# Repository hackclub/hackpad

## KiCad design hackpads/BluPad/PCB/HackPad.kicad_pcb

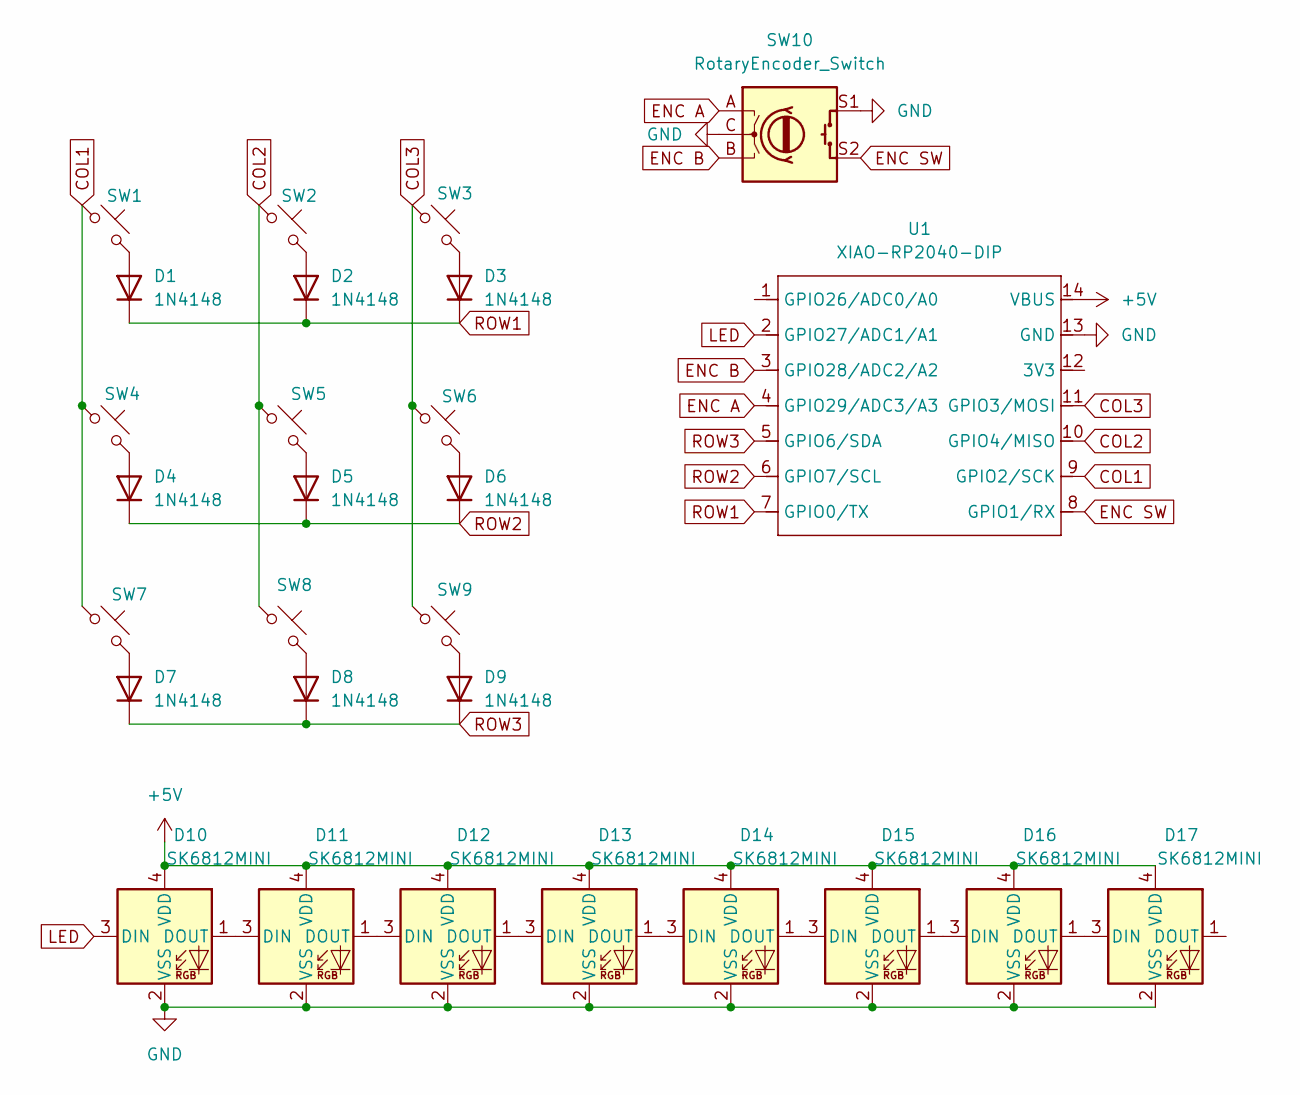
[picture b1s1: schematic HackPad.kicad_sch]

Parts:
D1, D2, D3, D4, D5, D6, D7, D8, D9: 1N4148; D_DO-35_SOD27_P7.62mm_Horizontal
D10, D11, D12, D13, D14, D15, D16, D17: SK6812MINI; LED_SK6812MINI_PLCC4_3.5x3.5mm_P1.75mm
SW1, SW2, SW3, SW4, SW5, SW6, SW7, SW8, SW9: SW_Push_45deg; SW_Cherry_MX_1.00u_PCB
SW10: RotaryEncoder_Switch; RotaryEncoder_Alps_EC11E-Switch_Vertical_H20mm
U1: XIAO-RP2040-DIP

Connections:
+5V: D10.4 (VDD), D11.4 (VDD), D12.4 (VDD), D13.4 (VDD), D14.4 (VDD), D15.4 (VDD), D16.4 (VDD), D17.4 (VDD), U1.14 (VBUS)
COL1: SW1.1, SW4.1, SW7.1, U1.9 (GPIO2/SCK)
COL2: SW2.1, SW5.1, SW8.1, U1.10 (GPIO4/MISO)
COL3: SW3.1, SW6.1, SW9.1, U1.11 (GPIO3/MOSI)
ENC A: SW10.A, U1.4 (GPIO29/ADC3/A3)
ENC B: SW10.B, U1.3 (GPIO28/ADC2/A2)
ENC SW: SW10.S2, U1.8 (GPIO1/RX)
GND: D10.2 (VSS), D11.2 (VSS), D12.2 (VSS), D13.2 (VSS), D14.2 (VSS), D15.2 (VSS), D16.2 (VSS), D17.2 (VSS), SW10.C, SW10.S1, U1.13 (GND)
LED: D10.3 (DIN), U1.2 (GPIO27/ADC1/A1)
unnamed: D1.2 (A), SW1.2
unnamed: D2.2 (A), SW2.2
unnamed: D3.2 (A), SW3.2
unnamed: D4.2 (A), SW4.2
unnamed: D5.2 (A), SW5.2
unnamed: D6.2 (A), SW6.2
unnamed: D7.2 (A), SW7.2
unnamed: D8.2 (A), SW8.2
unnamed: D9.2 (A), SW9.2
unnamed: D10.1 (DOUT), D11.3 (DIN)
unnamed: D11.1 (DOUT), D12.3 (DIN)
unnamed: D12.1 (DOUT), D13.3 (DIN)
unnamed: D13.1 (DOUT), D14.3 (DIN)
unnamed: D14.1 (DOUT), D15.3 (DIN)
unnamed: D15.1 (DOUT), D16.3 (DIN)
unnamed: D16.1 (DOUT), D17.3 (DIN)
ROW1: D1.1 (K), D2.1 (K), D3.1 (K), U1.7 (GPIO0/TX)
ROW2: D4.1 (K), D5.1 (K), D6.1 (K), U1.6 (GPIO7/SCL)
ROW3: D7.1 (K), D8.1 (K), D9.1 (K), U1.5 (GPIO6/SDA)

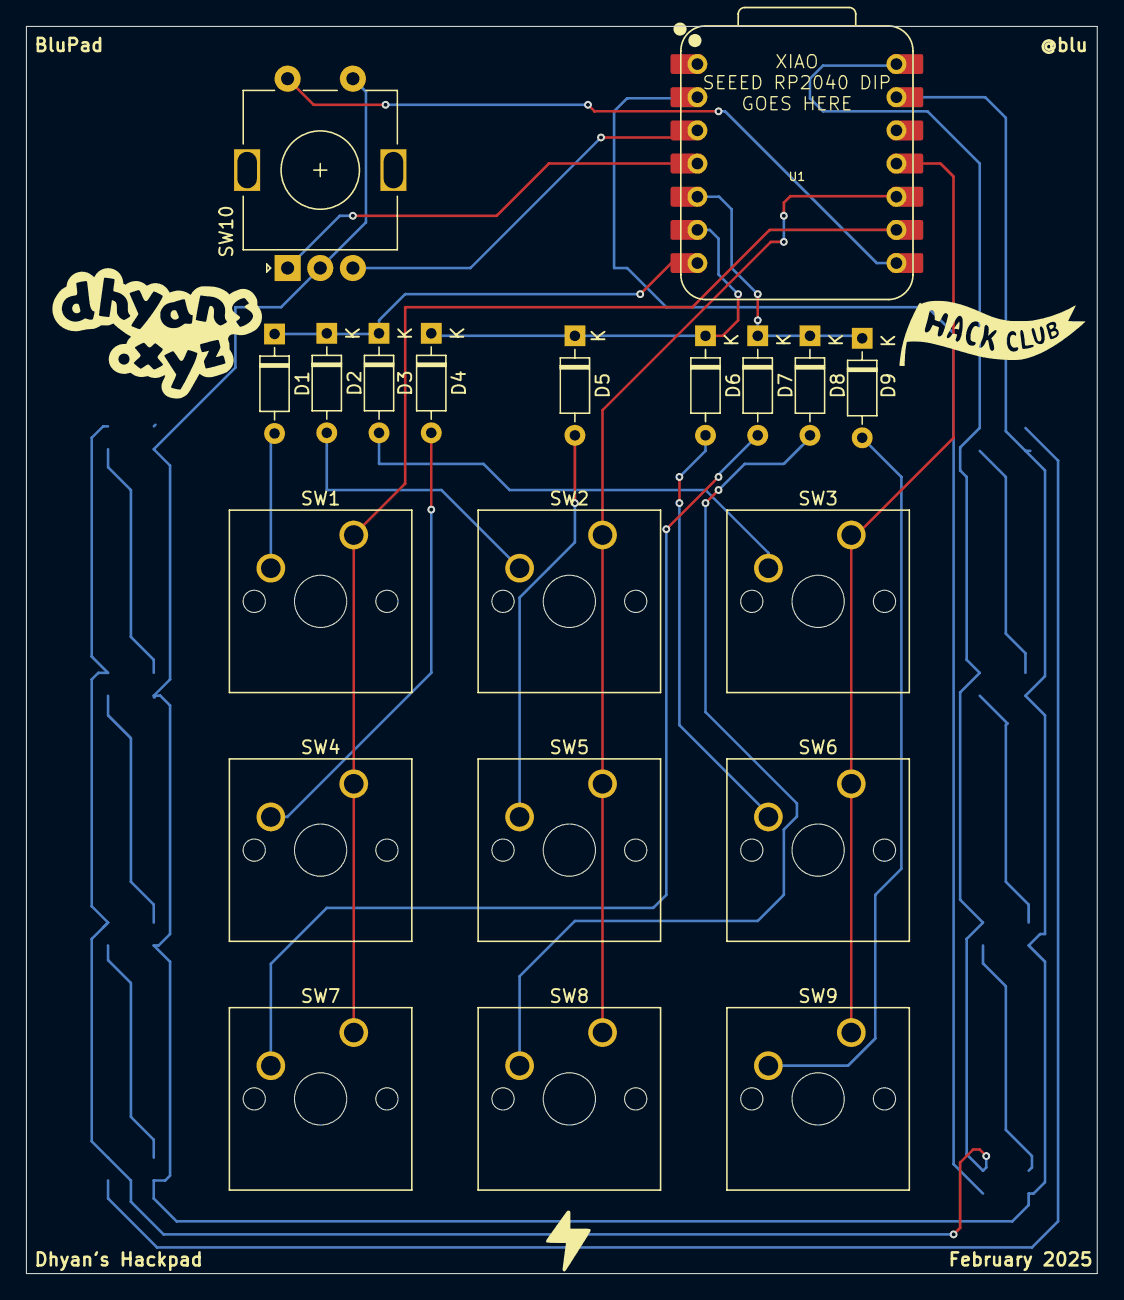
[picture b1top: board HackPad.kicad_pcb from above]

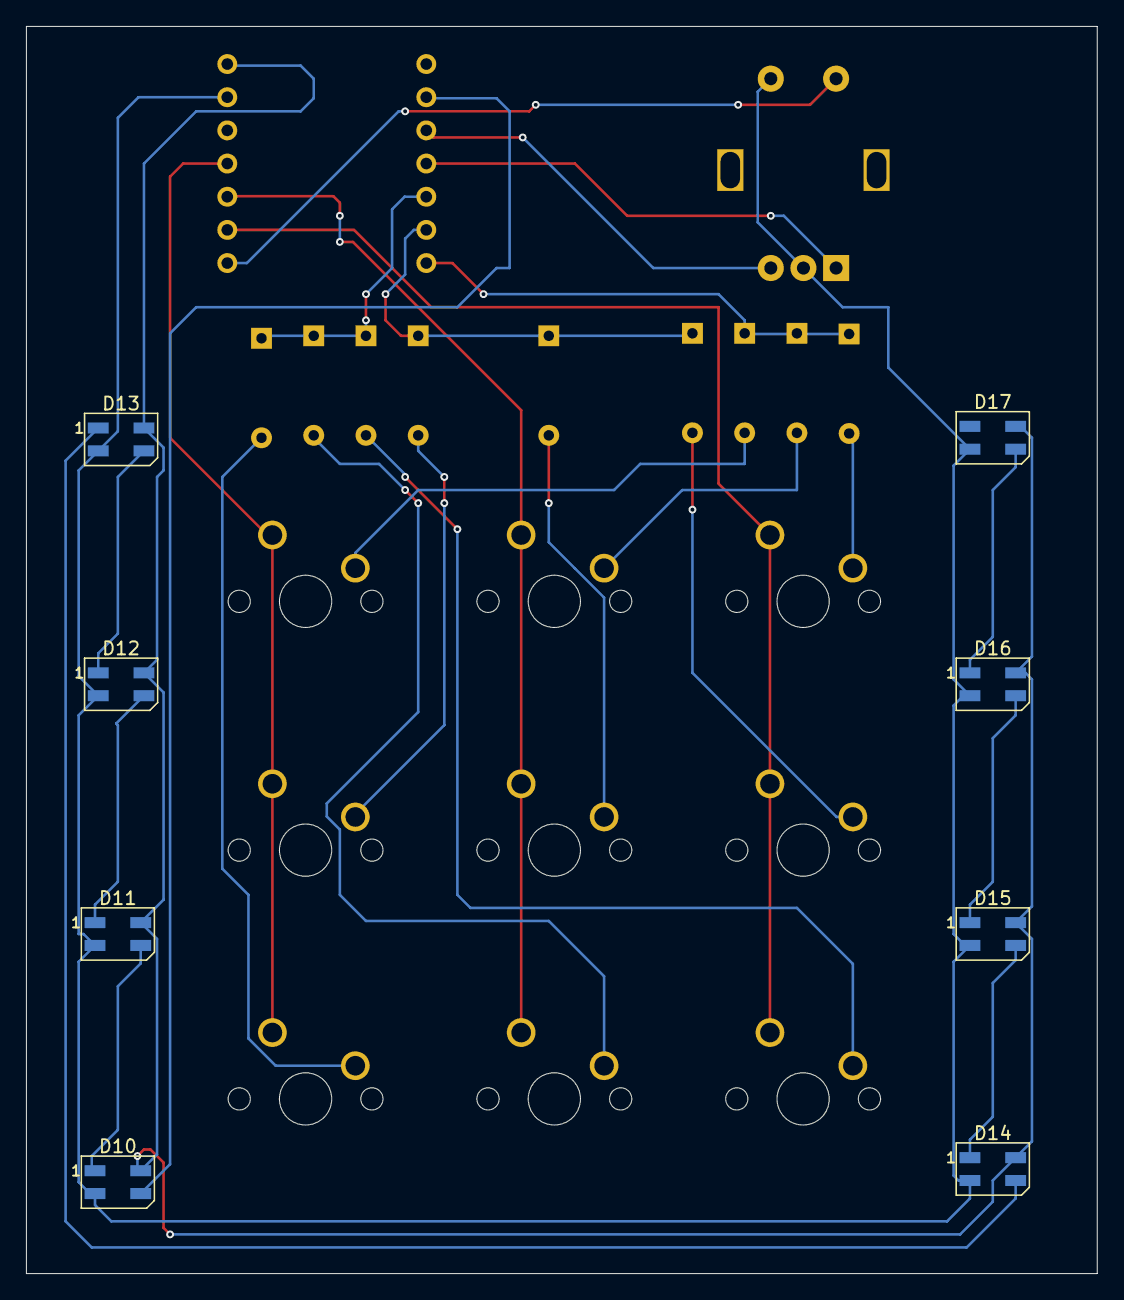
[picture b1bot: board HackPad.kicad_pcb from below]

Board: 2 copper layers, 82.0 x 95.5 mm, 28 parts (8 on the bottom side), 28 nets.

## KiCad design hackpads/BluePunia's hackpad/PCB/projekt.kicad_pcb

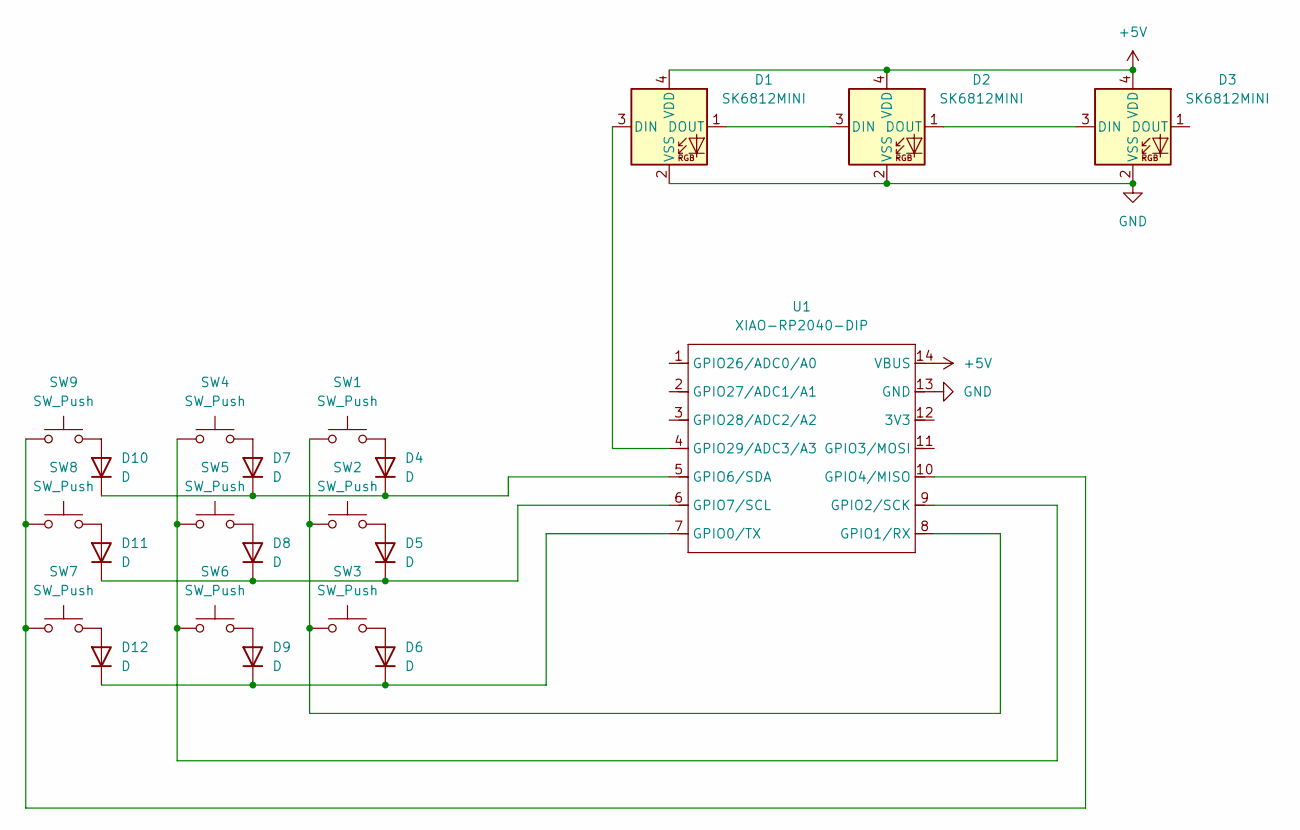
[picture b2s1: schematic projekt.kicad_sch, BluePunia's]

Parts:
D1, D2, D3: SK6812MINI; LED_SK6812MINI_PLCC4_3.5x3.5mm_P1.75mm
D4, D5, D6, D7, D8, D9, D10, D11, D12: D; D_DO-41_SOD81_P7.62mm_Horizontal
SW1, SW2, SW3, SW4, SW5, SW6, SW7, SW8, SW9: SW_Push; SW_Cherry_MX_1.00u_PCB
U1: XIAO-RP2040-DIP

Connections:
+5V: D1.4 (VDD), D2.4 (VDD), D3.4 (VDD), U1.14 (VBUS)
GND: D1.2 (VSS), D2.2 (VSS), D3.2 (VSS), U1.13 (GND)
unnamed: D1.3 (DIN), U1.4 (GPIO29/ADC3/A3)
unnamed: D1.1 (DOUT), D2.3 (DIN)
unnamed: D2.1 (DOUT), D3.3 (DIN)
unnamed: D4.2 (A), SW1.2
unnamed: D5.2 (A), SW2.2
unnamed: D6.2 (A), SW3.2
unnamed: D7.2 (A), SW4.2
unnamed: D8.2 (A), SW5.2
unnamed: D9.2 (A), SW6.2
unnamed: D10.2 (A), SW9.2
unnamed: D4.1 (K), D7.1 (K), D10.1 (K), U1.5 (GPIO6/SDA)
unnamed: D11.2 (A), SW8.2
unnamed: D5.1 (K), D8.1 (K), D11.1 (K), U1.6 (GPIO7/SCL)
unnamed: D12.2 (A), SW7.2
unnamed: D6.1 (K), D9.1 (K), D12.1 (K), U1.7 (GPIO0/TX)
unnamed: SW1.1, SW2.1, SW3.1, U1.8 (GPIO1/RX)
unnamed: SW4.1, SW5.1, SW6.1, U1.9 (GPIO2/SCK)
unnamed: SW7.1, SW8.1, SW9.1, U1.10 (GPIO4/MISO)

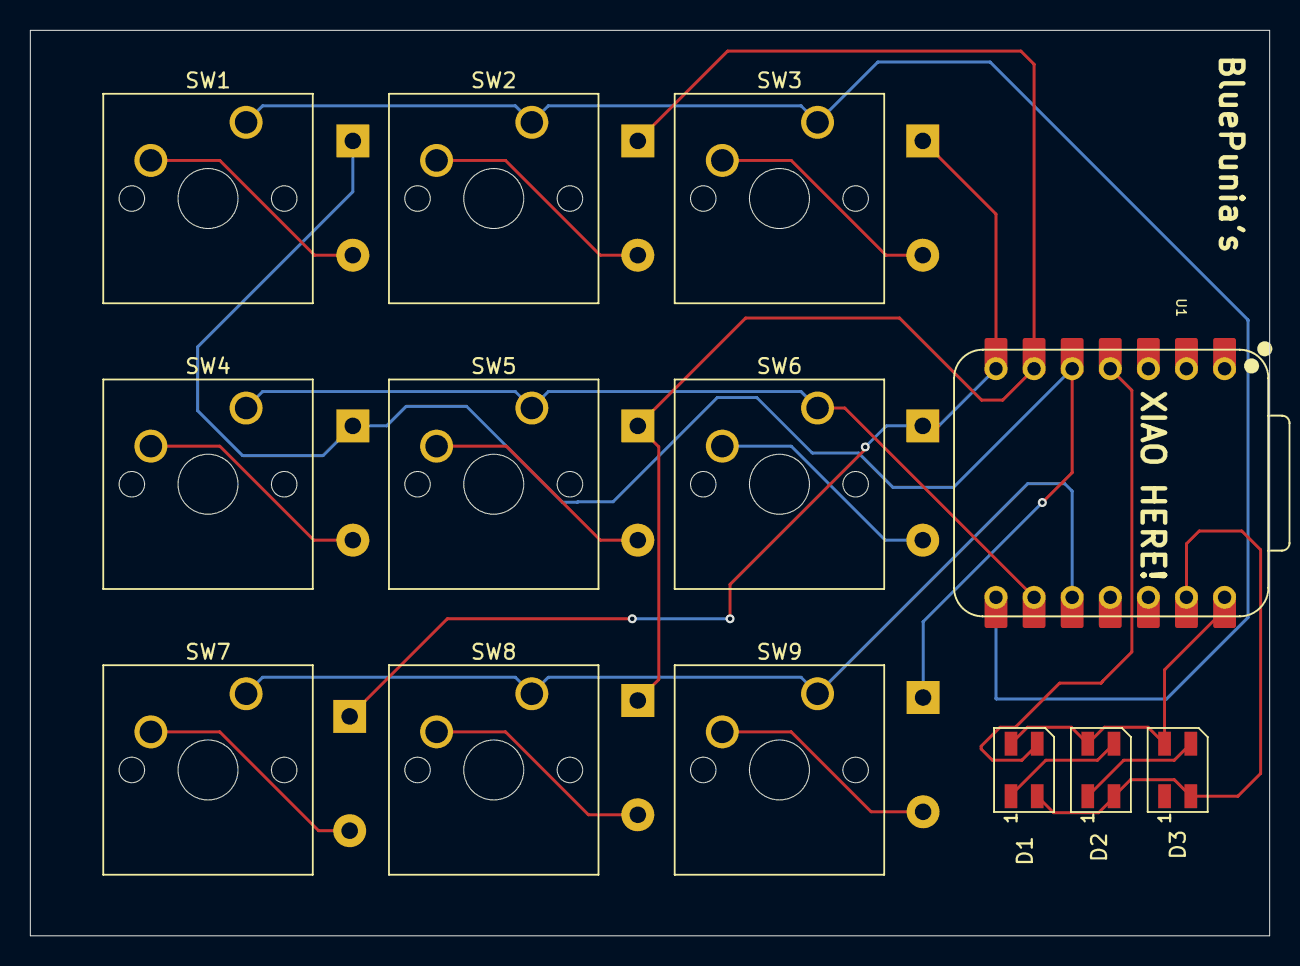
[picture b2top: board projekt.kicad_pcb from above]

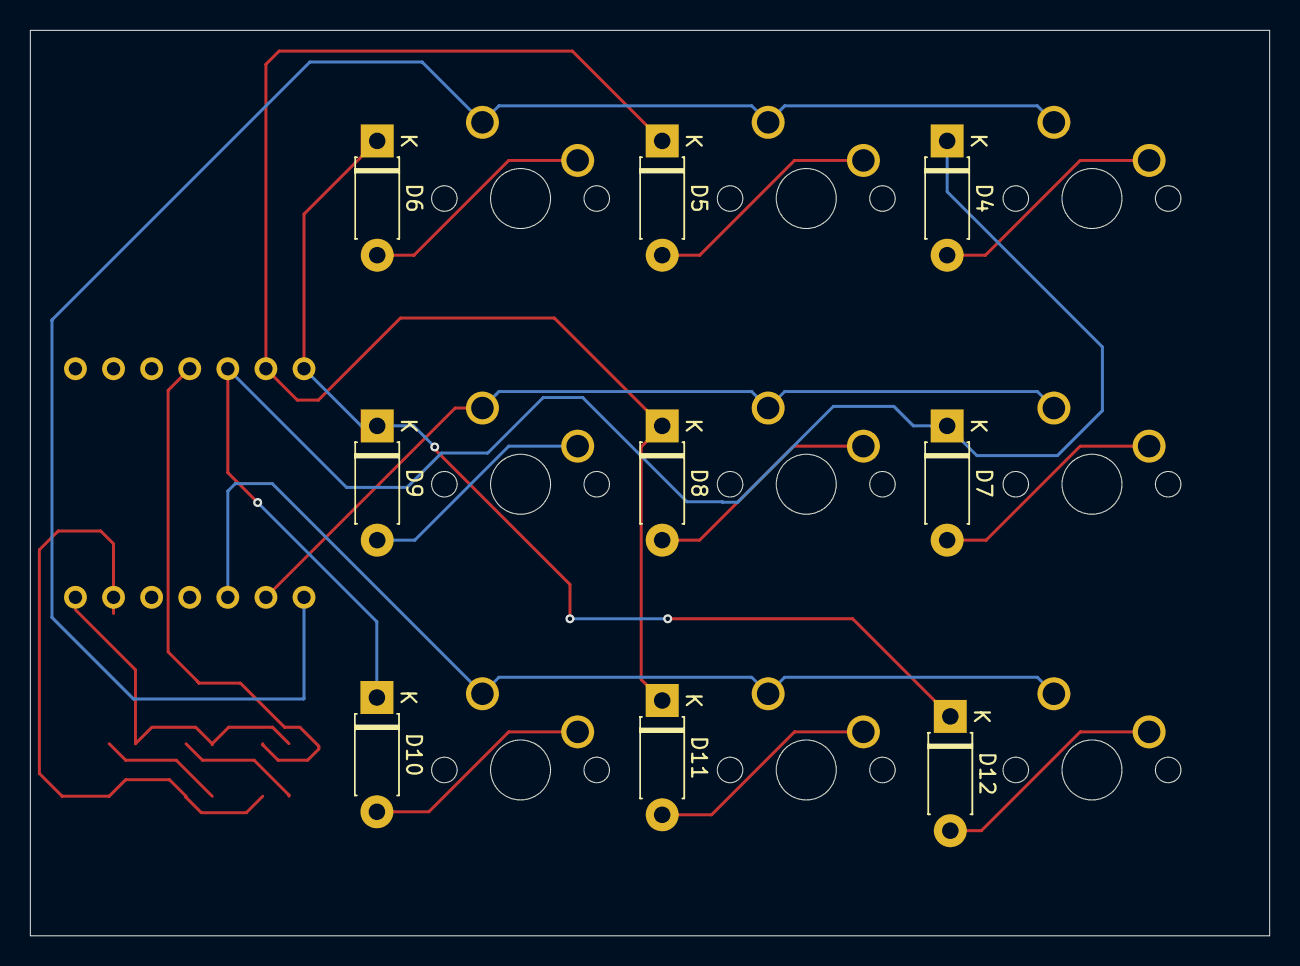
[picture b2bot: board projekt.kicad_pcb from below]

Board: 2 copper layers, 82.6 x 60.4 mm, 22 parts (9 on the bottom side), 20 nets.

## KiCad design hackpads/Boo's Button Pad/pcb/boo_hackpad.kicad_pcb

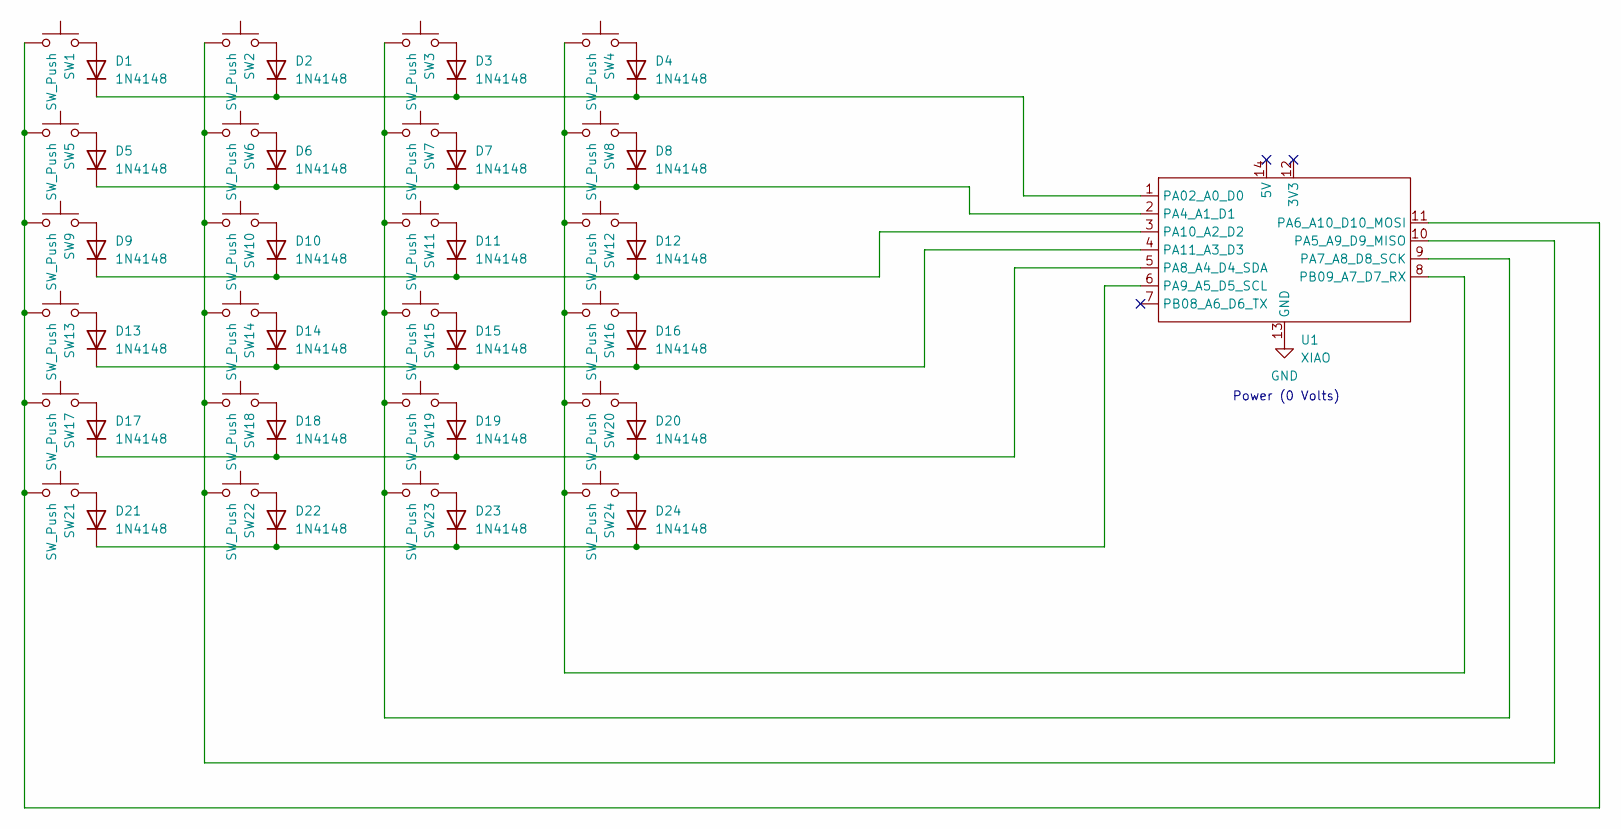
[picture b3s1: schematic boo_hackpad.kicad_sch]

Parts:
D1, D2, D3, D4, D5, D6, D7, D8, D9, D10, D11, D12, D13, D14, D15, D16, D17, D18, D19, D20, D21, D22, D23, D24: 1N4148; D_DO-35_SOD27_P7.62mm_Horizontal
SW1, SW2, SW3, SW4, SW5, SW6, SW7, SW8, SW9, SW10, SW11, SW12, SW13, SW14, SW15, SW16, SW17, SW18, SW19, SW20, SW21, SW22, SW23, SW24: SW_Push; SW_Cherry_MX_1.00u_PCB
U1: XIAO; XIAO-Generic-Hybrid-14P-2.54-21X17.8MM

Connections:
GND: U1.13 (GND)
unnamed: D1.2 (A), SW1.2
unnamed: D1.1 (K), D2.1 (K), D3.1 (K), D4.1 (K), U1.1 (PA02_A0_D0)
unnamed: D2.2 (A), SW2.2
unnamed: D3.2 (A), SW3.2
unnamed: D4.2 (A), SW4.2
unnamed: D5.2 (A), SW5.2
unnamed: D5.1 (K), D6.1 (K), D7.1 (K), D8.1 (K), U1.2 (PA4_A1_D1)
unnamed: D6.2 (A), SW6.2
unnamed: D7.2 (A), SW7.2
unnamed: D8.2 (A), SW8.2
unnamed: D9.2 (A), SW9.2
unnamed: D10.2 (A), SW10.2
unnamed: D9.1 (K), D10.1 (K), D11.1 (K), D12.1 (K), U1.3 (PA10_A2_D2)
unnamed: D11.2 (A), SW11.2
unnamed: D12.2 (A), SW12.2
unnamed: D13.2 (A), SW13.2
unnamed: D13.1 (K), D14.1 (K), D15.1 (K), D16.1 (K), U1.4 (PA11_A3_D3)
unnamed: D14.2 (A), SW14.2
unnamed: D15.2 (A), SW15.2
unnamed: D16.2 (A), SW16.2
unnamed: D17.2 (A), SW17.2
unnamed: D17.1 (K), D18.1 (K), D19.1 (K), D20.1 (K), U1.5 (PA8_A4_D4_SDA)
unnamed: D18.2 (A), SW18.2
unnamed: D19.2 (A), SW19.2
unnamed: D20.2 (A), SW20.2
unnamed: D21.2 (A), SW21.2
unnamed: D21.1 (K), D22.1 (K), D23.1 (K), D24.1 (K), U1.6 (PA9_A5_D5_SCL)
unnamed: D22.2 (A), SW22.2
unnamed: D23.2 (A), SW23.2
unnamed: D24.2 (A), SW24.2
unnamed: SW2.1, SW6.1, SW10.1, SW14.1, SW18.1, SW22.1, U1.10 (PA5_A9_D9_MISO)
unnamed: SW1.1, SW5.1, SW9.1, SW13.1, SW17.1, SW21.1, U1.11 (PA6_A10_D10_MOSI)
unnamed: SW3.1, SW7.1, SW11.1, SW15.1, SW19.1, SW23.1, U1.9 (PA7_A8_D8_SCK)
unnamed: SW4.1, SW8.1, SW12.1, SW16.1, SW20.1, SW24.1, U1.8 (PB09_A7_D7_RX)

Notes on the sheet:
Power (0 Volts)

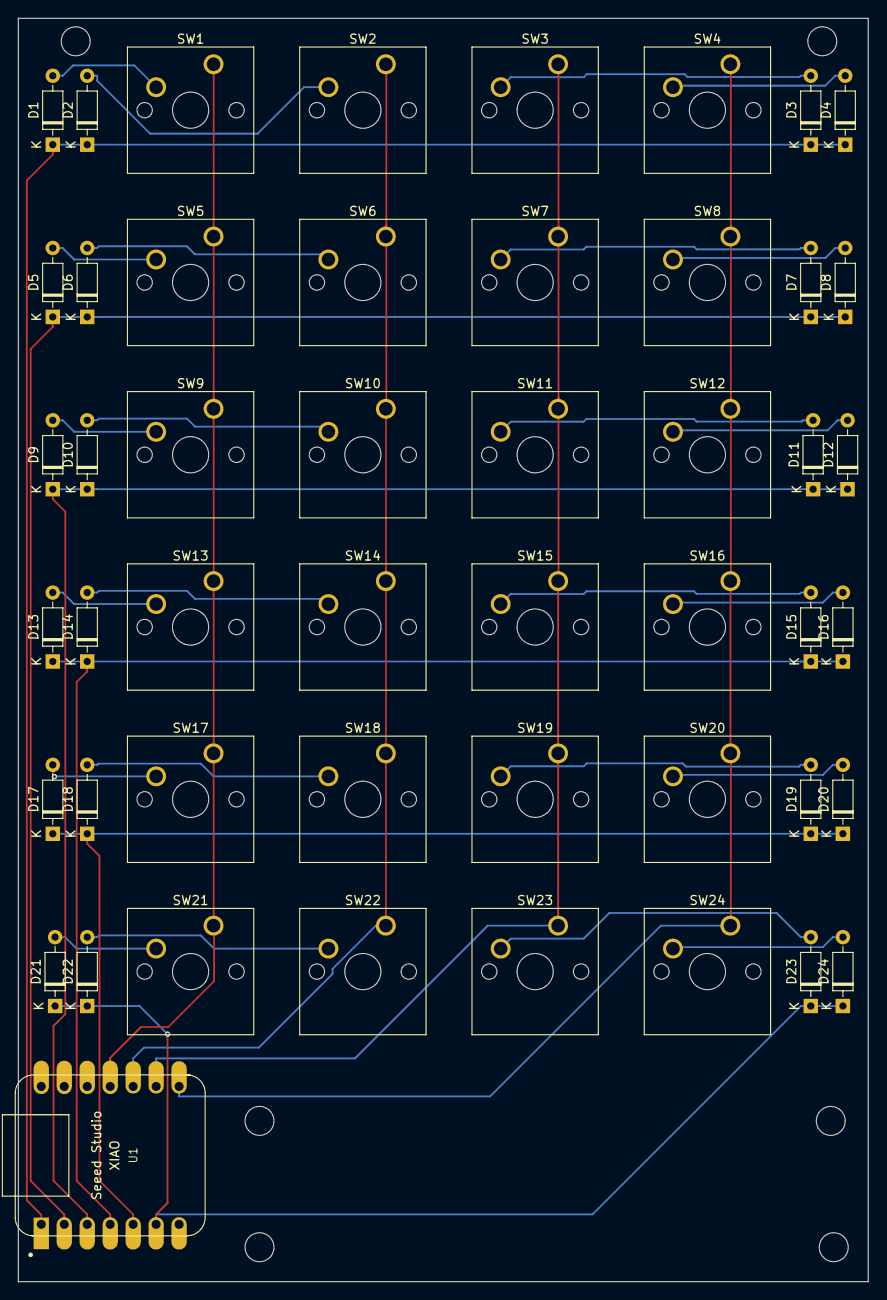
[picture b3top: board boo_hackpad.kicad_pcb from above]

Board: 2 copper layers, 94.0 x 139.7 mm, 49 parts (0 on the bottom side), 34 nets.

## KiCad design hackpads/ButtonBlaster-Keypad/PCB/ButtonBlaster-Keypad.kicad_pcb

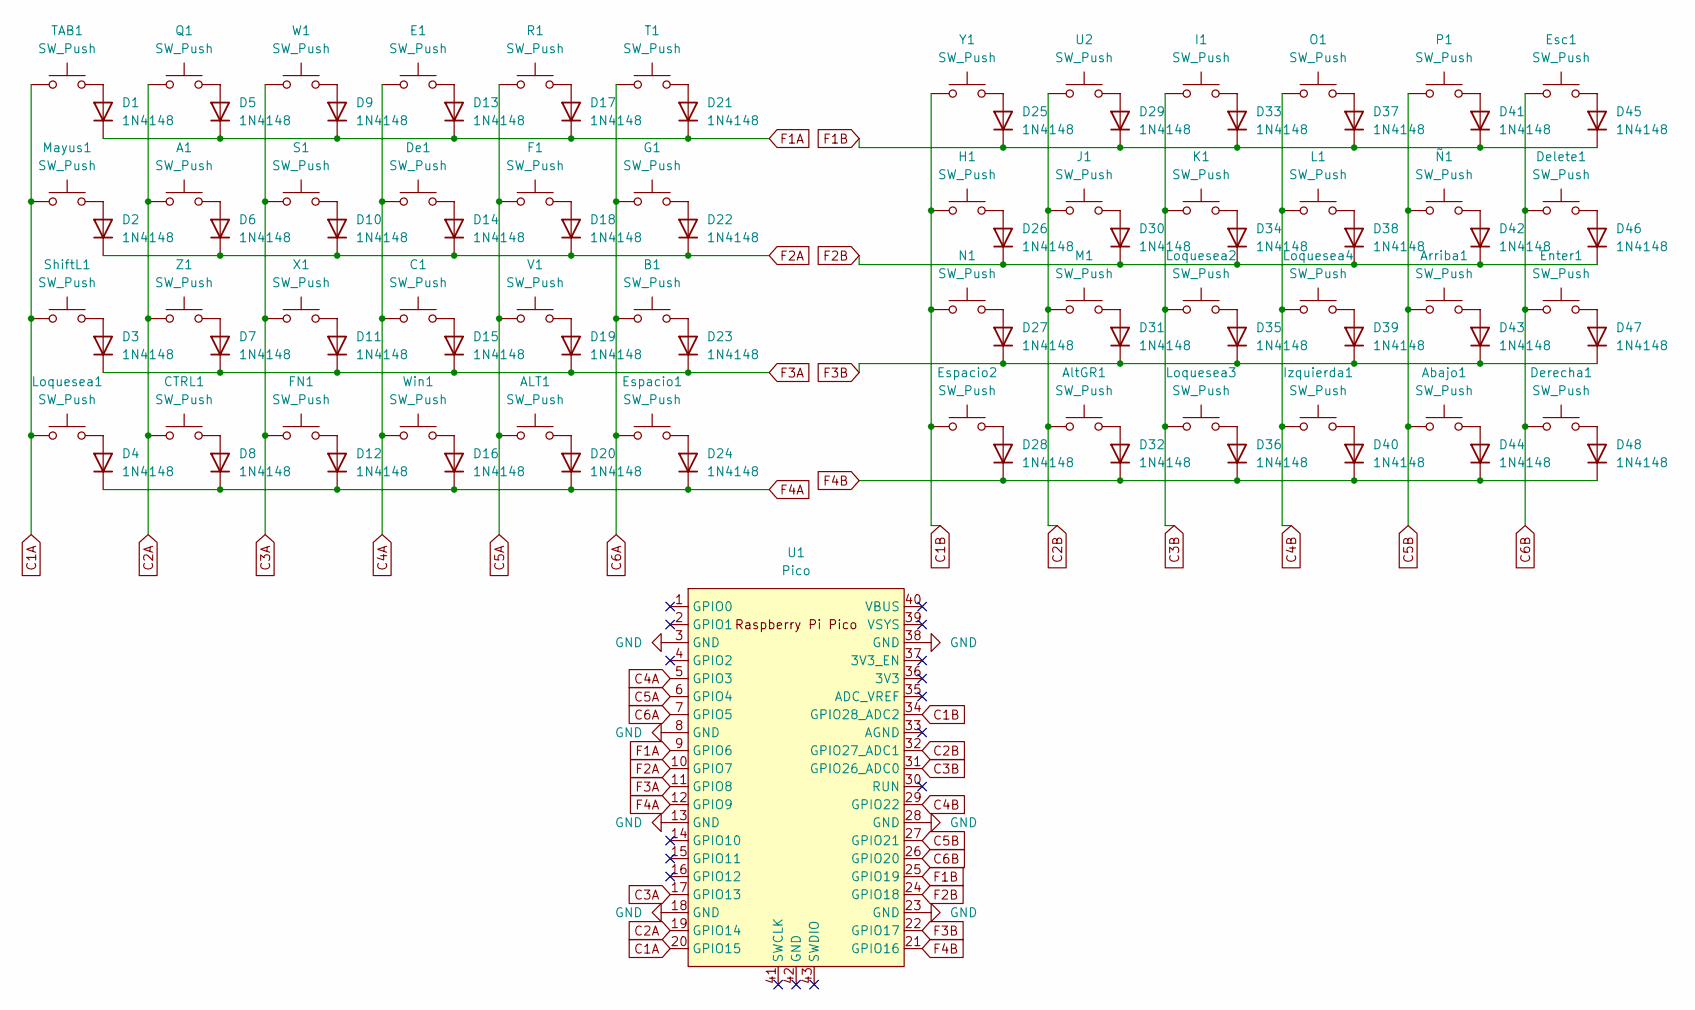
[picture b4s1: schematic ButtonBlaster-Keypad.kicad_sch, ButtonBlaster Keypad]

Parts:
A1: SW_Push; SW_Cherry_MX_1.00u_PCB
ALT1: SW_Push; SW_Cherry_MX_1.00u_PCB
Abajo1: SW_Push; SW_Cherry_MX_1.00u_PCB
AltGR1: SW_Push; SW_Cherry_MX_1.00u_PCB
Arriba1: SW_Push; SW_Cherry_MX_1.00u_PCB
B1: SW_Push; SW_Cherry_MX_1.00u_PCB
C1: SW_Push; SW_Cherry_MX_1.00u_PCB
CTRL1: SW_Push; SW_Cherry_MX_1.00u_PCB
D1, D2, D3, D4, D5, D6, D7, D8, D9, D10, D11, D12, D13, D14, D15, D16, D17, D18, D19, D20, D21, D22, D23, D24, D25, D26, D27, D28, D29, D30, D31, D32, D33, D34, D35, D36, D37, D38, D39, D40, D41, D42, D43, D44, D45, D46, D47, D48: 1N4148; D_DO-35_SOD27_P7.62mm_Horizontal
De1: SW_Push; SW_Cherry_MX_1.00u_PCB
Delete1: SW_Push; SW_Cherry_MX_1.00u_PCB
Derecha1: SW_Push; SW_Cherry_MX_1.00u_PCB
E1: SW_Push; SW_Cherry_MX_1.00u_PCB
Enter1: SW_Push; SW_Cherry_MX_1.00u_PCB
Esc1: SW_Push; SW_Cherry_MX_1.00u_PCB
Espacio1, Espacio2: SW_Push; SW_Cherry_MX_1.00u_PCB
F1: SW_Push; SW_Cherry_MX_1.00u_PCB
FN1: SW_Push; SW_Cherry_MX_1.00u_PCB
G1: SW_Push; SW_Cherry_MX_1.00u_PCB
H1: SW_Push; SW_Cherry_MX_1.00u_PCB
I1: SW_Push; SW_Cherry_MX_1.00u_PCB
Izquierda1: SW_Push; SW_Cherry_MX_1.00u_PCB
J1: SW_Push; SW_Cherry_MX_1.00u_PCB
K1: SW_Push; SW_Cherry_MX_1.00u_PCB
L1: SW_Push; SW_Cherry_MX_1.00u_PCB
Loquesea1, Loquesea2, Loquesea3, Loquesea4: SW_Push; SW_Cherry_MX_1.00u_PCB
M1: SW_Push; SW_Cherry_MX_1.00u_PCB
Mayus1: SW_Push; SW_Cherry_MX_1.00u_PCB
N1: SW_Push; SW_Cherry_MX_1.00u_PCB
O1: SW_Push; SW_Cherry_MX_1.00u_PCB
P1: SW_Push; SW_Cherry_MX_1.00u_PCB
Q1: SW_Push; SW_Cherry_MX_1.00u_PCB
R1: SW_Push; SW_Cherry_MX_1.00u_PCB
S1: SW_Push; SW_Cherry_MX_1.00u_PCB
ShiftL1: SW_Push; SW_Cherry_MX_1.00u_PCB
T1: SW_Push; SW_Cherry_MX_1.00u_PCB
TAB1: SW_Push; SW_Cherry_MX_1.00u_PCB
U1: Pico; RPi_Pico_SMD_TH
U2: SW_Push; SW_Cherry_MX_1.00u_PCB
V1: SW_Push; SW_Cherry_MX_1.00u_PCB
W1: SW_Push; SW_Cherry_MX_1.00u_PCB
Win1: SW_Push; SW_Cherry_MX_1.00u_PCB
X1: SW_Push; SW_Cherry_MX_1.00u_PCB
Y1: SW_Push; SW_Cherry_MX_1.00u_PCB
Z1: SW_Push; SW_Cherry_MX_1.00u_PCB
Ñ1: SW_Push; SW_Cherry_MX_1.00u_PCB

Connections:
C1A: Loquesea1.1, Mayus1.1, ShiftL1.1, TAB1.1, U1.20 (GPIO15)
C1B: Espacio2.1, H1.1, N1.1, U1.34 (GPIO28_ADC2), Y1.1
C2A: A1.1, CTRL1.1, Q1.1, U1.19 (GPIO14), Z1.1
C2B: AltGR1.1, J1.1, M1.1, U1.32 (GPIO27_ADC1), U2.1
C3A: FN1.1, S1.1, U1.17 (GPIO13), W1.1, X1.1
C3B: I1.1, K1.1, Loquesea2.1, Loquesea3.1, U1.31 (GPIO26_ADC0)
C4A: C1.1, De1.1, E1.1, U1.5 (GPIO3), Win1.1
C4B: Izquierda1.1, L1.1, Loquesea4.1, O1.1, U1.29 (GPIO22)
C5A: ALT1.1, F1.1, R1.1, U1.6 (GPIO4), V1.1
C5B: Abajo1.1, Arriba1.1, P1.1, U1.27 (GPIO21), Ñ1.1
C6A: B1.1, Espacio1.1, G1.1, T1.1, U1.7 (GPIO5)
C6B: Delete1.1, Derecha1.1, Enter1.1, Esc1.1, U1.26 (GPIO20)
F1A: D1.1 (K), D5.1 (K), D9.1 (K), D13.1 (K), D17.1 (K), D21.1 (K), U1.9 (GPIO6)
F1B: D25.1 (K), D29.1 (K), D33.1 (K), D37.1 (K), D41.1 (K), D45.1 (K), U1.25 (GPIO19)
F2A: D2.1 (K), D6.1 (K), D10.1 (K), D14.1 (K), D18.1 (K), D22.1 (K), U1.10 (GPIO7)
F2B: D26.1 (K), D30.1 (K), D34.1 (K), D38.1 (K), D42.1 (K), D46.1 (K), U1.24 (GPIO18)
F3A: D3.1 (K), D7.1 (K), D11.1 (K), D15.1 (K), D19.1 (K), D23.1 (K), U1.11 (GPIO8)
F3B: D27.1 (K), D31.1 (K), D35.1 (K), D39.1 (K), D43.1 (K), D47.1 (K), U1.22 (GPIO17)
F4A: D4.1 (K), D8.1 (K), D12.1 (K), D16.1 (K), D20.1 (K), D24.1 (K), U1.12 (GPIO9)
F4B: D28.1 (K), D32.1 (K), D36.1 (K), D40.1 (K), D44.1 (K), D48.1 (K), U1.21 (GPIO16)
GND: U1.3 (GND), U1.8 (GND), U1.13 (GND), U1.18 (GND), U1.23 (GND), U1.28 (GND), U1.38 (GND)
unnamed: D1.2 (A), TAB1.2
unnamed: D2.2 (A), Mayus1.2
unnamed: D3.2 (A), ShiftL1.2
unnamed: D4.2 (A), Loquesea1.2
unnamed: D5.2 (A), Q1.2
unnamed: A1.2, D6.2 (A)
unnamed: D7.2 (A), Z1.2
unnamed: CTRL1.2, D8.2 (A)
unnamed: D9.2 (A), W1.2
unnamed: D10.2 (A), S1.2
unnamed: D11.2 (A), X1.2
unnamed: D12.2 (A), FN1.2
unnamed: D13.2 (A), E1.2
unnamed: D14.2 (A), De1.2
unnamed: C1.2, D15.2 (A)
unnamed: D16.2 (A), Win1.2
unnamed: D17.2 (A), R1.2
unnamed: D18.2 (A), F1.2
unnamed: D19.2 (A), V1.2
unnamed: ALT1.2, D20.2 (A)
unnamed: D21.2 (A), T1.2
unnamed: D22.2 (A), G1.2
unnamed: B1.2, D23.2 (A)
unnamed: D24.2 (A), Espacio1.2
unnamed: D25.2 (A), Y1.2
unnamed: D26.2 (A), H1.2
unnamed: D27.2 (A), N1.2
unnamed: D28.2 (A), Espacio2.2
unnamed: D29.2 (A), U2.2
unnamed: D30.2 (A), J1.2
unnamed: D31.2 (A), M1.2
unnamed: AltGR1.2, D32.2 (A)
unnamed: D33.2 (A), I1.2
unnamed: D34.2 (A), K1.2
unnamed: D35.2 (A), Loquesea2.2
unnamed: D36.2 (A), Loquesea3.2
unnamed: D37.2 (A), O1.2
unnamed: D38.2 (A), L1.2
unnamed: D39.2 (A), Loquesea4.2
unnamed: D40.2 (A), Izquierda1.2
unnamed: D41.2 (A), P1.2
unnamed: D42.2 (A), Ñ1.2
unnamed: Arriba1.2, D43.2 (A)
unnamed: Abajo1.2, D44.2 (A)
unnamed: D45.2 (A), Esc1.2
unnamed: D46.2 (A), Delete1.2
unnamed: D47.2 (A), Enter1.2
unnamed: D48.2 (A), Derecha1.2

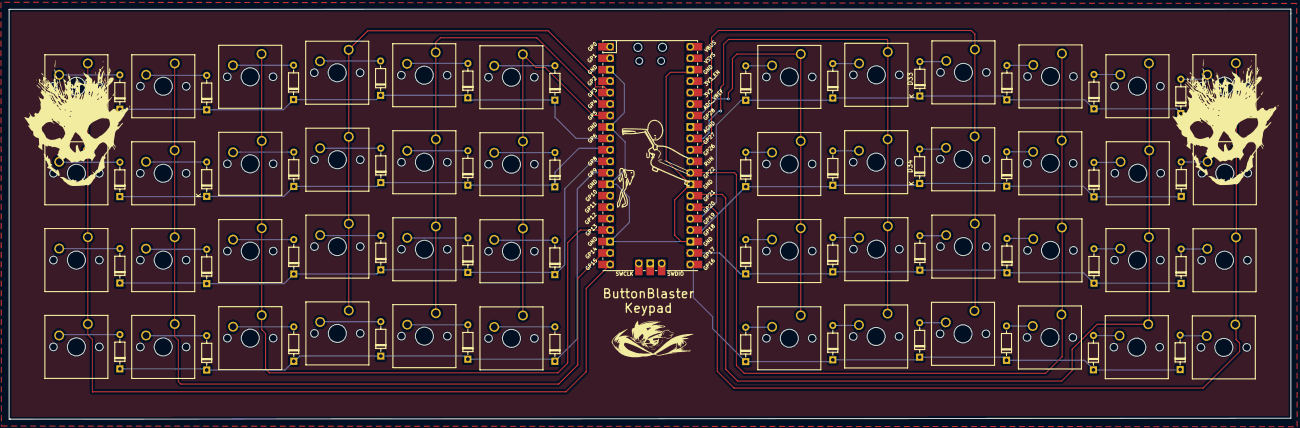
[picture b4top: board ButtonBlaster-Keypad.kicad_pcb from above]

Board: 2 copper layers, 284.1 x 90.9 mm, 97 parts (0 on the bottom side), 69 nets.

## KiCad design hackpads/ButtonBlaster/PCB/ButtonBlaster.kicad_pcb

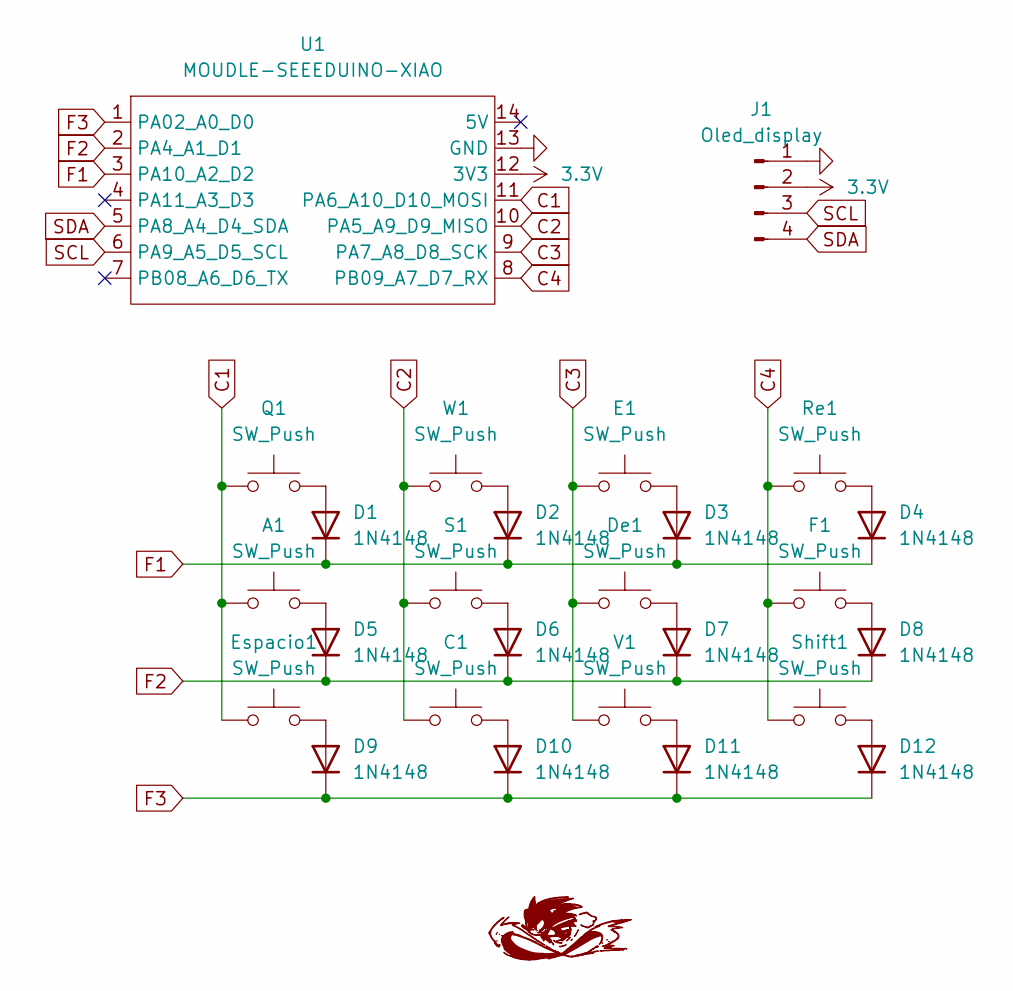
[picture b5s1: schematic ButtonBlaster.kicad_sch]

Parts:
A1: SW_Push; SW_Cherry_MX_1.00u_PCB
C1: SW_Push; SW_Cherry_MX_1.00u_PCB
D1, D2, D3, D4, D5, D6, D7, D8, D9, D10, D11, D12: 1N4148; D_DO-35_SOD27_P7.62mm_Horizontal
De1: SW_Push; SW_Cherry_MX_1.00u_PCB
E1: SW_Push; SW_Cherry_MX_1.00u_PCB
Espacio1: SW_Push; SW_Cherry_MX_1.00u_PCB
F1: SW_Push; SW_Cherry_MX_1.00u_PCB
J1: Oled_display; SSD1306-0.91-OLED-4pin-128x32
Q1: SW_Push; SW_Cherry_MX_1.00u_PCB
Re1: SW_Push; SW_Cherry_MX_1.00u_PCB
S1: SW_Push; SW_Cherry_MX_1.00u_PCB
Shift1: SW_Push; SW_Cherry_MX_1.00u_PCB
U1: MOUDLE-SEEEDUINO-XIAO; XIAO-Generic-Hybrid-14P-2.54-21X17.8MM
V1: SW_Push; SW_Cherry_MX_1.00u_PCB
W1: SW_Push; SW_Cherry_MX_1.00u_PCB

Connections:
3.3V: J1.2, U1.12 (3V3)
C1: A1.1, Espacio1.1, Q1.1, U1.11 (PA6_A10_D10_MOSI)
C2: C1.1, S1.1, U1.10 (PA5_A9_D9_MISO), W1.1
C3: De1.1, E1.1, U1.9 (PA7_A8_D8_SCK), V1.1
C4: F1.1, Re1.1, Shift1.1, U1.8 (PB09_A7_D7_RX)
F1: D1.1 (K), D2.1 (K), D3.1 (K), D4.1 (K), U1.3 (PA10_A2_D2)
F2: D5.1 (K), D6.1 (K), D7.1 (K), D8.1 (K), U1.2 (PA4_A1_D1)
F3: D9.1 (K), D10.1 (K), D11.1 (K), D12.1 (K), U1.1 (PA02_A0_D0)
GND: J1.1, U1.13 (GND)
unnamed: D1.2 (A), Q1.2
unnamed: D2.2 (A), W1.2
unnamed: D3.2 (A), E1.2
unnamed: D4.2 (A), Re1.2
unnamed: A1.2, D5.2 (A)
unnamed: D6.2 (A), S1.2
unnamed: D7.2 (A), De1.2
unnamed: D8.2 (A), F1.2
unnamed: D9.2 (A), Espacio1.2
unnamed: C1.2, D10.2 (A)
unnamed: D11.2 (A), V1.2
unnamed: D12.2 (A), Shift1.2
SCL: J1.3, U1.6 (PA9_A5_D5_SCL)
SDA: J1.4, U1.5 (PA8_A4_D4_SDA)

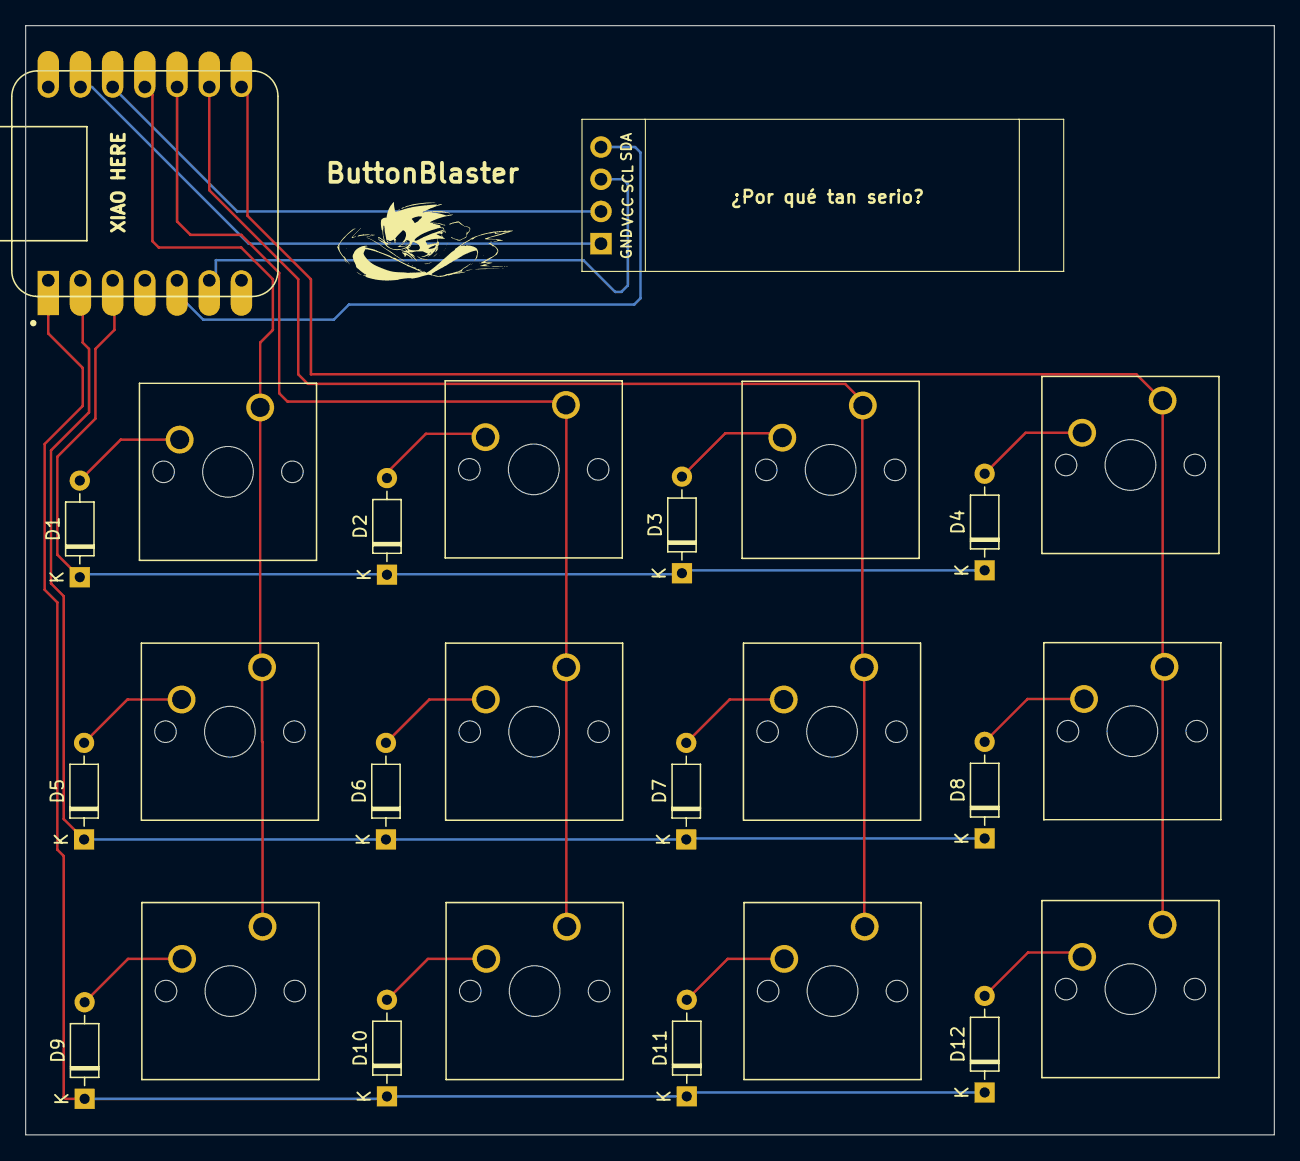
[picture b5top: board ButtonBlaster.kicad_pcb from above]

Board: 2 copper layers, 98.5 x 87.5 mm, 26 parts (0 on the bottom side), 23 nets.
